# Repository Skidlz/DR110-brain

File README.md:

# DR-110 Brain

A new screen, CPU, and PCB for the Boss DR-110 drum machine

Work in progress

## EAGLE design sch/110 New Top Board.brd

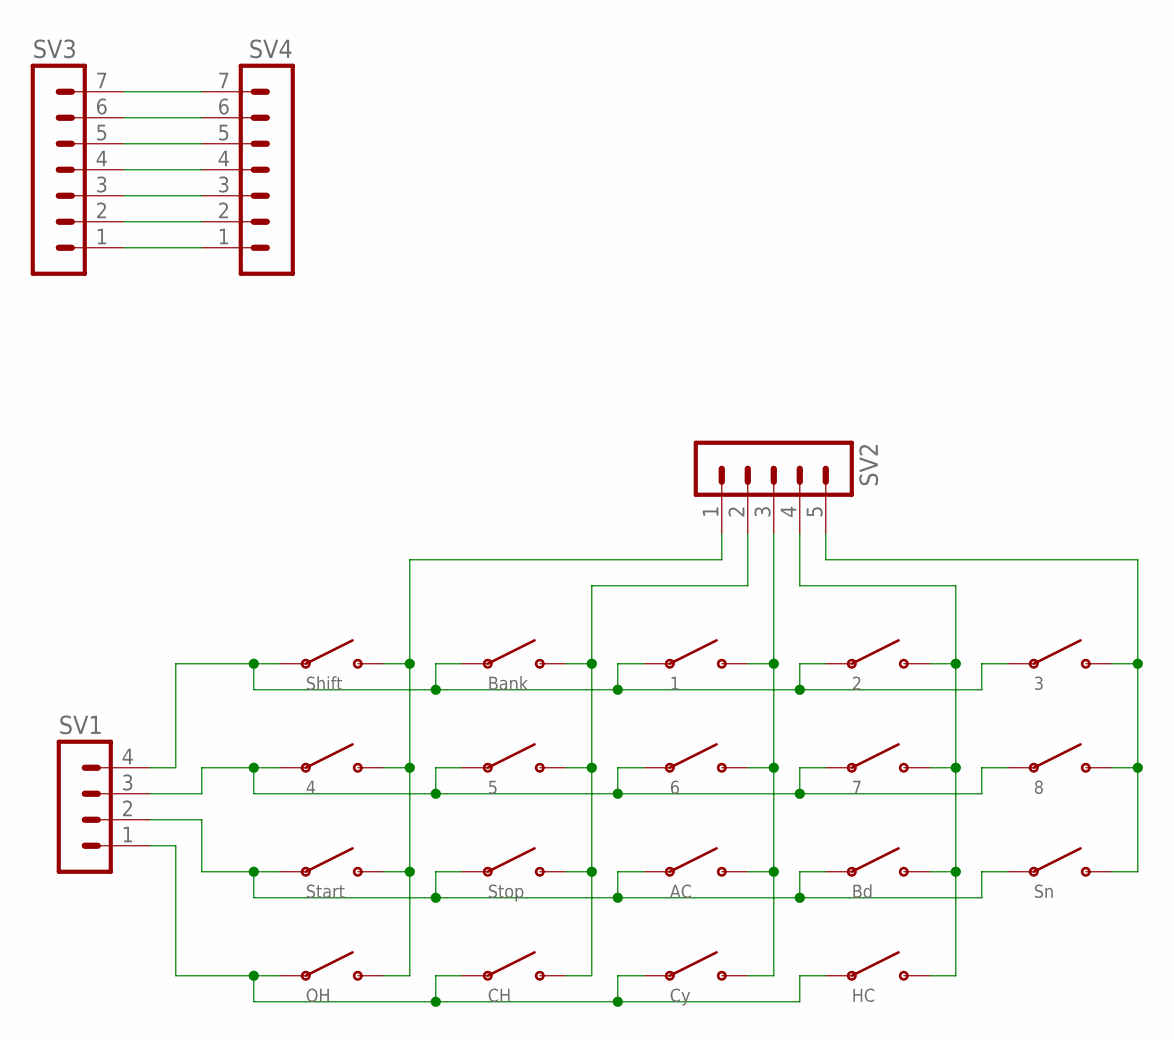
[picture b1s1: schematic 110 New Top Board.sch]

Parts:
SV1: MA04-1
SV2: MA05-1
SV3, SV4: MA07-1
U$1: AC; DR110-PAD
U$2: Bd; DR110-PAD
U$3: Sn; DR110-PAD
U$4: OH; DR110-PAD
U$5: CH; DR110-PAD
U$6: Cy; DR110-PAD
U$7: HC; DR110-PAD
U$8: Shift; DR110-PAD
U$9: Bank; DR110-PAD
U$10: 1; DR110-PAD
U$11: 2; DR110-PAD
U$12: 3; DR110-PAD
U$13: 4; DR110-PAD
U$14: 5; DR110-PAD
U$15: 6; DR110-PAD
U$16: 7; DR110-PAD
U$17: 8; DR110-PAD
U$19: Start; DR110-PAD
U$20: Stop; DR110-PAD

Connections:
unnamed: SV1.1, U$4.P$1, U$5.P$1, U$6.P$1, U$7.P$1
unnamed: SV2.1, U$4.P$2, U$8.P$2, U$13.P$2, U$19.P$2
unnamed: SV2.2, U$5.P$2, U$9.P$2, U$14.P$2, U$20.P$2
unnamed: SV2.3, U$1.P$2, U$6.P$2, U$10.P$2, U$15.P$2
unnamed: SV1.2, U$1.P$1, U$2.P$1, U$3.P$1, U$19.P$1, U$20.P$1
unnamed: SV1.3, U$13.P$1, U$14.P$1, U$15.P$1, U$16.P$1, U$17.P$1
unnamed: SV3.1, SV4.1
unnamed: SV1.4, U$8.P$1, U$9.P$1, U$10.P$1, U$11.P$1, U$12.P$1
unnamed: SV3.2, SV4.2
unnamed: SV3.3, SV4.3
unnamed: SV2.4, U$2.P$2, U$7.P$2, U$11.P$2, U$16.P$2
unnamed: SV2.5, U$3.P$2, U$12.P$2, U$17.P$2
unnamed: SV3.4, SV4.4
unnamed: SV3.5, SV4.5
unnamed: SV3.6, SV4.6
unnamed: SV3.7, SV4.7

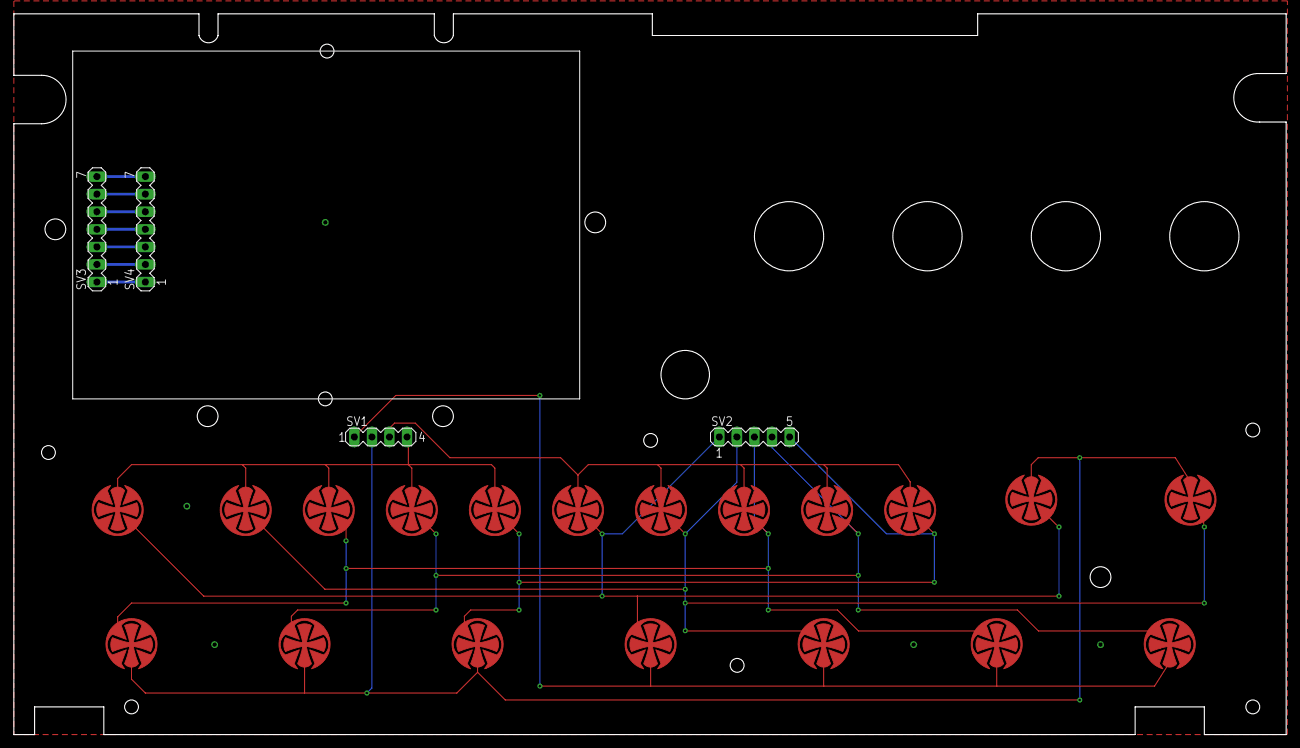
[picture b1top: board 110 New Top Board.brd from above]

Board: 2 copper layers, 183.8 x 104.1 mm, 23 parts (0 on the bottom side), 16 nets.

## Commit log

2025-12-07 Init src
2025-12-07 Init eagle files
2025-12-07 init img
